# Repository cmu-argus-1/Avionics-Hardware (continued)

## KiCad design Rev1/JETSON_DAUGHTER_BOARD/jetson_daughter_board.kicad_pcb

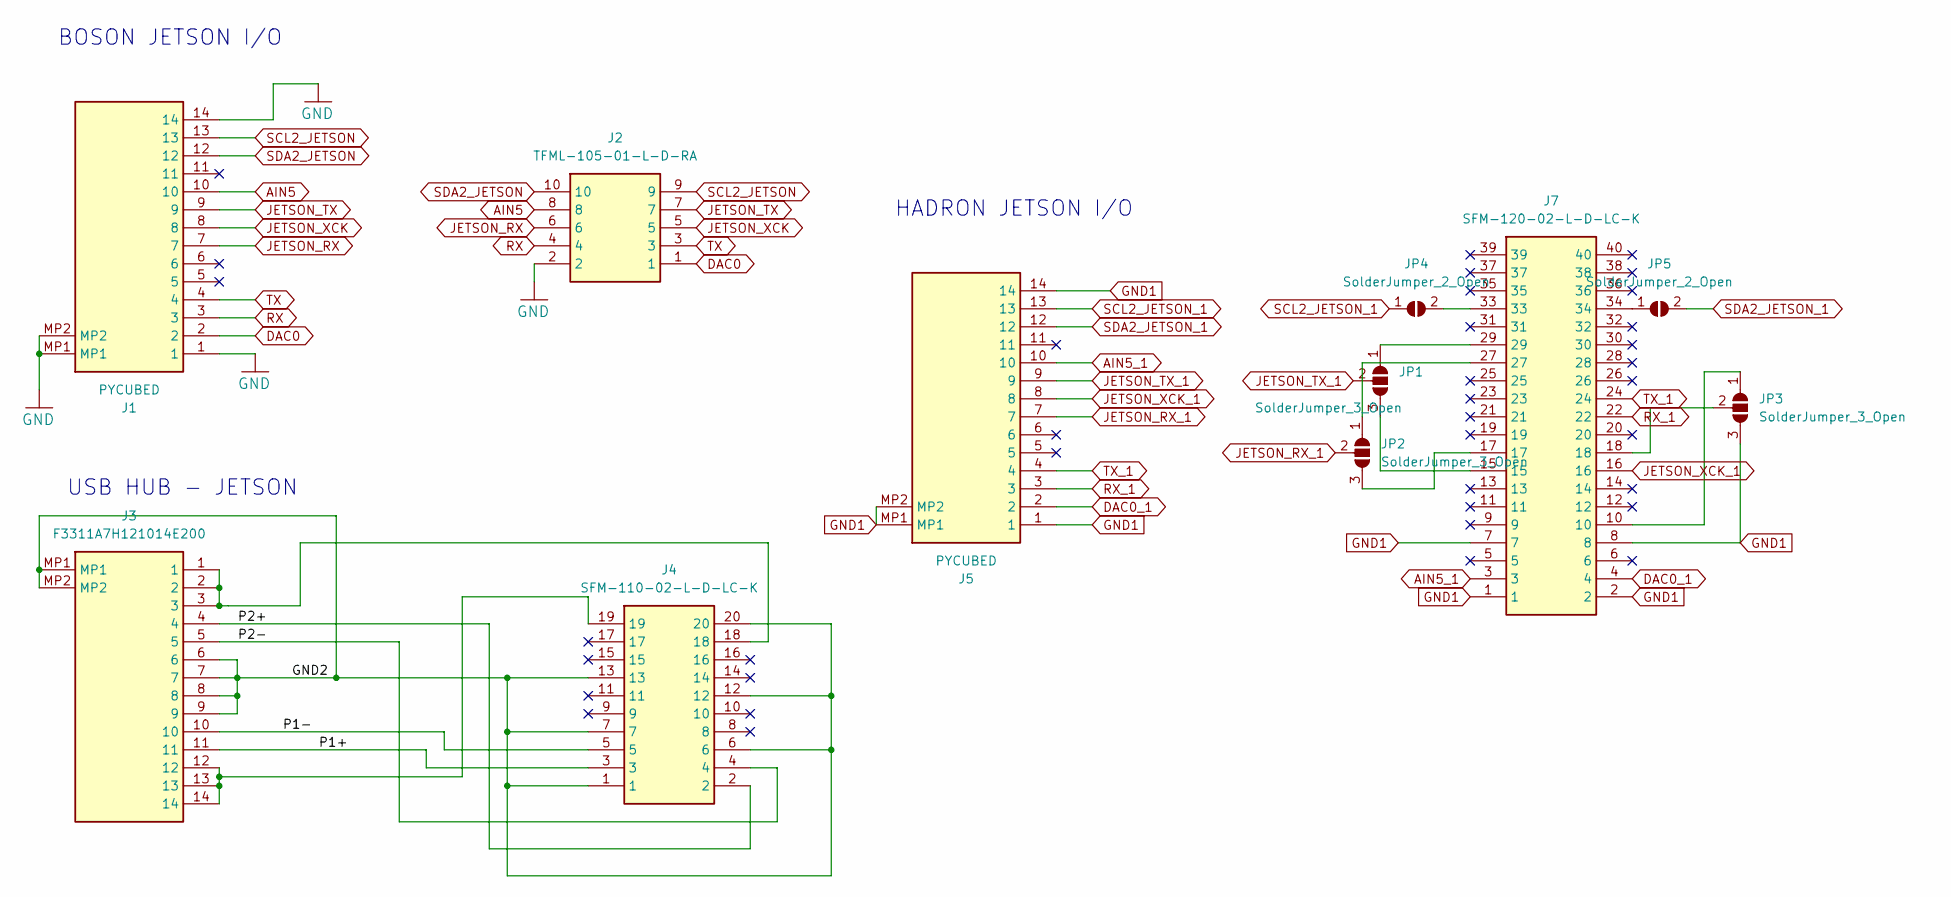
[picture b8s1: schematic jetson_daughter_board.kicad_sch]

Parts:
J1, J5: PYCUBED; F3311A7H121014E200; Manufacturer_Part_Number F3311A7H121014E200
J2: TFML-105-01-L-D-RA; TFML10501LDRA; Manufacturer_Part_Number TFML-105-01-L-D-RA; Mouser Part Number 200-TFML10501LDRA
J3: F3311A7H121014E200; Manufacturer_Part_Number F3311A7H121014E200
J4: SFM-110-02-L-D-LC-K; SFM11002LDLCK; Manufacturer_Part_Number SFM-110-02-L-D-LC-K; Mouser Part Number 200-SFM11002LDLCK
J7: SFM-120-02-L-D-LC-K; SFM12002LDLCK; Manufacturer_Part_Number SFM-120-02-L-D-LC-K; Mouser Part Number 200-SFM12002LDLCK
JP1, JP2, JP3: SolderJumper_3_Open; SolderJumper-3_P1.3mm_Open_Pad1.0x1.5mm
JP4, JP5: SolderJumper_2_Open; SolderJumper-2_P1.3mm_Open_Pad1.0x1.5mm

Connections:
/GND2: J3.6, J3.7, J3.8, J3.9, J3.MP1, J3.MP2, J4.1, J4.6, J4.7, J4.12, J4.13, J4.20
/P1+: J3.11, J4.3
/P1-: J3.10, J4.5
/P2+: J3.4, J4.2
/P2-: J3.5, J4.4
AIN5: J1.10, J2.8
AIN5_1: J5.10, J7.3
DAC0: J1.2, J2.1
DAC0_1: J5.2, J7.4
GND: J1.1, J1.14, J1.MP1, J1.MP2, J2.2
GND1: J5.1, J5.14, J5.MP1, J5.MP2, J7.1, J7.2, J7.7, J7.8, JP3.3 (B)
JETSON_RX: J1.7, J2.6
JETSON_RX_1: J5.7, JP2.2 (C)
JETSON_TX: J1.9, J2.7
JETSON_TX_1: J5.9, JP1.2 (C)
JETSON_XCK: J1.8, J2.5
JETSON_XCK_1: J5.8, J7.16
unnamed: J3.1, J3.2, J3.3, J4.18
unnamed: J3.12, J3.13, J3.14, J4.19
unnamed: J7.29, JP1.1 (A)
unnamed: J7.15, JP1.3 (B)
unnamed: J7.27, JP2.1 (A)
unnamed: J7.17, JP2.3 (B)
unnamed: J7.10, JP3.1 (A)
unnamed: J7.18, JP3.2 (C)
unnamed: J7.33, JP4.2 (B)
unnamed: J7.34, JP5.1 (A)
RX: J1.3, J2.4
RX_1: J5.3, J7.22
SCL2_JETSON: J1.13, J2.9
SCL2_JETSON_1: J5.13, JP4.1 (A)
SDA2_JETSON: J1.12, J2.10
SDA2_JETSON_1: J5.12, JP5.2 (B)
TX: J1.4, J2.3
TX_1: J5.4, J7.24

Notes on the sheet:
USB HUB - JETSON
BOSON JETSON I/O
HADRON JETSON I/O

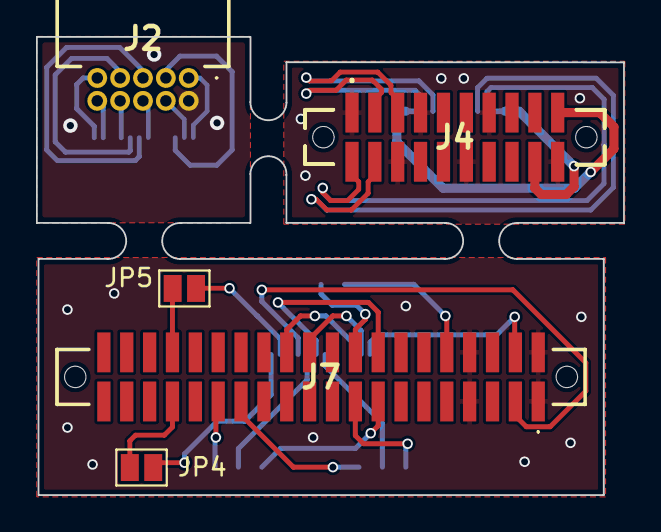
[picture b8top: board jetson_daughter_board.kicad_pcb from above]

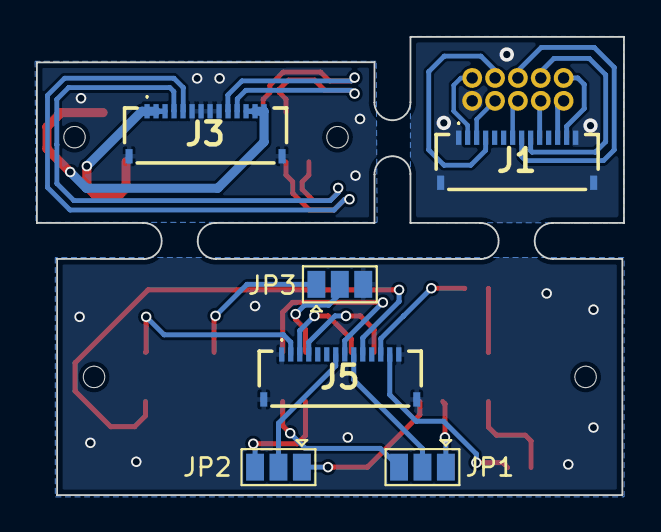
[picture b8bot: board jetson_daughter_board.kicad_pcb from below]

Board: 2 copper layers, 32.6 x 25.5 mm, 11 parts (6 on the bottom side), 35 nets.

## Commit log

2023-09-25 Update README.md
    added description
2023-09-25 added MTC_driver board
2023-09-25 added example board said in website
2023-09-27 pulled sample board
2023-10-04 Create Battery Board Directory
2023-10-04 Pulled from PyCubed batteryboard-v01b
2023-10-09 Schematic Verified
2023-10-09 made changes to brd
2023-10-11 pull
2023-10-11 added gerber files
2023-10-11 added parts list
2023-10-20 Update for Auto Backup files
2023-10-21 copied template
2023-10-21 added new board
2023-10-22 modified board and schematic for x panel
2023-11-08 changes made
2023-11-08 need to add solar panel and solar sensor
    added all coils and routed the planes.
2023-11-09 Solar Cells BOM
2023-11-15 wrong outline x panel
2023-11-15 updated z axis
2023-11-15 Started intial coil loop on first layer on Z-Axis board
2023-11-22 Added 52 loops of coil trace wiring on first 2 layers of z-axis battery board
2023-11-28 completed z axis board
2023-11-28 incremental changes
2023-12-02 Finished 2 coil layers of XPanel_V0 board
2023-12-04 Made first 2 layers identical for XPANEL_V0 Board
2023-12-05 Finished 6 Layers of colis for XPANELV0 Board, but needs validation
2024-01-24 made changes
2024-01-25 redid coils for Xpanel board under Solar Panel Argus 54 coils on each layer - 2 layers total
2024-01-26 Battery Board Final Update
2024-01-26 made custom footprints and symbols for both solar panels-custom lib also created and added to files
2024-01-26 made changes to Z axis with new cutout
2024-01-26 CHANGED file structure
2024-01-26 N-1 Z camera board - smt connector left to add
2024-01-26 Updated the FPC Connections
    FPC connector is reversable now
2024-01-26 made changes to xy board
2024-01-26 PyCubed Schematic Update
2024-01-26 Made changes to LTC ; remaining switches for H bridge and LTC3130 for 70mm panel
2024-01-26 Schematic lock on XY BOARD
2024-01-26 PyCubed Schematic Finalized
2024-01-27 PyCubed Interface Connectors Placed
2024-01-27 Moved some stuff around
2024-01-27 completed XY Board
2024-01-27 Cleared DRC and signoff
2024-01-27 PyCubed Routing Done
2024-01-28 PyCubed DRCs Rectified
2024-01-28 cleared All warnings and DRC
2024-01-28 added logo
2024-01-29 created step
2024-01-29 changed directory structure , z panel schematics done.
2024-01-29 added 3d model
2024-01-29 made changes with feedback
2024-01-29 incr changes
2024-01-29 made changes according to feedback
2024-01-29 Battery Board Updated based on Feedback
2024-01-29 Battery Board all changes done
    Based on feedback by Neil
2024-01-30 added buck for coil driver
2024-01-30 made changes to the board
2024-01-30 final push XY board with step updated
2024-02-01 added dxf to z plus. incremental update
2024-02-02 made changes to Z plus board
2024-02-02 Mainboard Final Design
    Updated BMS
2024-02-03 initial routing z plus
2024-02-05 Added KiCad .gitignore
2024-02-05 Repo gitignore cleanup. Push PyCubed DRC updates
2024-02-05 Add schematic bak files to gitignore
2024-02-05 Removed kicad_sch-bak files
2024-02-05 Designed Jetson Daughter Board
2024-02-07 REV 1.0 ZPLUS
2024-02-09 ADDED BOM FOR PYCUBED
2024-02-19 Directory Restructured
2024-02-19 Sending all bom excel documents
2024-02-19 BOMs Updated
2024-02-21 Finished Torque Coils on Camera Board 52 loops each on 2 layers
2024-02-23 Create readme.md
    added checklist
2024-02-23 Updated all the checklist
2024-02-23 ADDED README
2024-02-23 added updates on cutouts
2024-02-23 changed resistor sizes;
2024-02-23 made changes to Z minus and Z plus cutouts
2024-02-24 finished Z minus board design
2024-02-24 updated status
2024-02-24 added step file for mechanical signoff
2024-02-24 fixed bug in Z minus
2024-02-24 changes silkscreen
2024-02-25 fixed bugs and finished Z plus
2024-02-25 updated status of PCB
2024-02-25 USB HUB Completed
2024-02-25 Directory Cleanup
2024-02-26 CHANGED Resistor values for MPPC; added testpoints and silkscreen info
2024-02-27 USB HUB Finalized
2024-02-27 Checkoff
2024-02-28 Updated USB HUB
    Based on Mechanical Feedback
2024-02-28 USB_HUB Thickness Changed
2024-02-28 Jetson Daughter Boards Updated
2024-02-28 Jetson Daughter Board Updated
    Added solder jumpers for i2c lines
2024-03-03 USB HUB Updated
    Based on TA feedback
2024-03-04 made diode changes and schematic changes
2024-03-04 updated ltc3130 schematic
2024-03-04 updated boards
2024-03-04 added antenna FP
2024-03-04 generated ibom
2024-03-04 Z minus done
2024-03-04 SIGNOFF:NISCHAL Z MINUS
2024-03-04 updated cap footprint
2024-03-04 final z minus nischal signioff
2024-03-04 USB HUB Update and directory cleanup
2024-03-04 Z PLUS Updated
2024-03-04 Daughter Board Updated
2024-03-04 changed pads
2024-03-04 cleared drc with updated rules
2024-03-04 Z Plus DRCs cleared
2024-03-14 added board and outline
2024-03-14 changed layer stack
2024-03-15 Z torque coils done for 2 layers 54 loops each
2024-03-16 added scehmatic
2024-03-18 incremental update
2024-03-18 GENERATED BOM
2024-03-18 final signoff by nischal
2024-03-25 made layer changes and sent out the board
2024-03-25 added step
2024-03-25 edited put the small vias from DRV8830 footprint
2024-03-26 Changed orientation of Z Torque
2024-03-26 Added Mech_Avi Interface CSV
2024-03-27 made changes to step
2024-04-03 Created USB HUB Rev 1.1
2024-04-04 Updated USB HUB Rev 1.1
2024-04-07 BOM Cleanup
2024-04-16 Designed Battery Board Rev 2
2024-04-16 Batteryboard Rev. 2 Signoff
2024-04-18 Rev 3 XY Panel Torquers 2 Layers done (53 loops each)
2024-07-02 Repo Re-structure
2024-07-19 Upload completed v1 boards
2024-07-27 Upload Jetson Carrier v1
2024-09-10 Step file relabel for compatibility
2024-10-22 Deployables added
2024-10-24 Upload Z- Board model
2025-01-08 Upload Coil Tester boards
